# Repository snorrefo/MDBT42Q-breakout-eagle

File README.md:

# MDBT42Q-breakout-eagle
Eagle files for making a breakout board for Raytac's MDBT42Q - nRF52832 based BLE module

Ordered MDBT42Q modules from [Tinysine](https://www.tinyosshop.com/mdbt42-ble-module), due to low shipping to Norway. $7.95 each, plus $4 shipping to Norway. Alternative: [Seed](https://www.seeedstudio.com/MDBT42Q-nRF52832-based-BLE-module-p-2736.html) 

Uploaded MDBT42Q.brd and ordered board from [OSH Park](https://oshpark.com/shared_projects/iggYdmAZ). Link contains shared project, ready for order. $9.80 per batch of three.

Uploaded MDBT42Q.brd and ordered solder stencil and acrylic jig set from [OSH Stencils](https://www.oshstencils.com/) for 10 $ + 5 $ shipping to Norway. Stencil Polyimide Film 3mil (0.003").

Used lead-free solder paste from [SparkFun/Chip Quik](https://www.sparkfun.com/products/12878).

After applying solder paste using the stencil, jig set and solder paste spreader (included in the jig set), the MDBT42Q module was placed gently on top of the solder and board. It doesn't matter much that the solder is smeared a bit, as the reflow will draw the solder to the solder pads. 

The board was placed in an old springform cake tin, and placed on a kitchen stove plate to reflow the solder. Turning the plate on, I used a digital cooking thermometer placed under some tin foil to monitor the cake tin temperature. My thermometer read ca. 223 deg C when the solder paste had reflowed properly. See solder paste data sheet for recommended reflow temperature profile (max 249 deg C). When the solder had reflowed properly, the cake tin was removed from the hot plate to cool. The result:

Using a JTAG programmer, such as the one included on Nordic's [nRF52 Developer Kit](https://www.nordicsemi.com/eng/Products/Bluetooth-low-energy/nRF52-DK), I was able to program the MDBT42Q module. More on that later. See for example 

https://learn.sparkfun.com/tutorials/nrf52832-breakout-board-hookup-guide

https://devzone.nordicsemi.com/f/nordic-q-a/14058/external-programming-using-nrf52-dk

Connecting the nRF52 DK to the MDBT42Q:

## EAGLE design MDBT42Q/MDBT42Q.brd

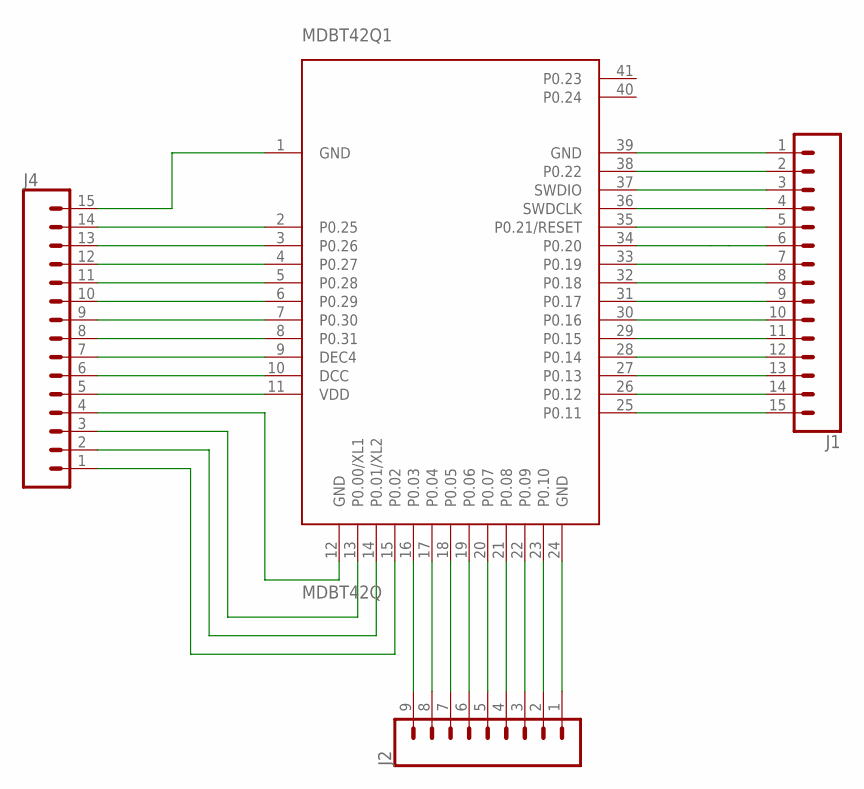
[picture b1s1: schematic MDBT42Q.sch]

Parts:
J1, J4: CONN_15; 1X15
J2: CONN_09; 1X09
MDBT42Q1: MDBT42Q

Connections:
unnamed: J4.15, MDBT42Q1.1 (GND)
unnamed: J4.14, MDBT42Q1.2 (P0.25)
unnamed: J4.13, MDBT42Q1.3 (P0.26)
unnamed: J4.12, MDBT42Q1.4 (P0.27)
unnamed: J4.11, MDBT42Q1.5 (P0.28)
unnamed: J4.10, MDBT42Q1.6 (P0.29)
unnamed: J4.9, MDBT42Q1.7 (P0.30)
unnamed: J4.8, MDBT42Q1.8 (P0.31)
unnamed: J4.7, MDBT42Q1.9 (DEC4)
unnamed: J4.6, MDBT42Q1.10 (DCC)
unnamed: J4.5, MDBT42Q1.11 (VDD)
unnamed: J4.4, MDBT42Q1.12 (GND)
unnamed: J4.3, MDBT42Q1.13 (P0.00/XL1)
unnamed: J4.2, MDBT42Q1.14 (P0.01/XL2)
unnamed: J4.1, MDBT42Q1.15 (P0.02)
unnamed: J2.9, MDBT42Q1.16 (P0.03)
unnamed: J2.8, MDBT42Q1.17 (P0.04)
unnamed: J2.5, MDBT42Q1.20 (P0.07)
unnamed: J2.6, MDBT42Q1.19 (P0.06)
unnamed: J2.7, MDBT42Q1.18 (P0.05)
unnamed: J2.4, MDBT42Q1.21 (P0.08)
unnamed: J2.3, MDBT42Q1.22 (P0.09)
unnamed: J2.2, MDBT42Q1.23 (P0.10)
unnamed: J2.1, MDBT42Q1.24 (GND)
unnamed: J1.15, MDBT42Q1.25 (P0.11)
unnamed: J1.14, MDBT42Q1.26 (P0.12)
unnamed: J1.13, MDBT42Q1.27 (P0.13)
unnamed: J1.12, MDBT42Q1.28 (P0.14)
unnamed: J1.11, MDBT42Q1.29 (P0.15)
unnamed: J1.10, MDBT42Q1.30 (P0.16)
unnamed: J1.9, MDBT42Q1.31 (P0.17)
unnamed: J1.8, MDBT42Q1.32 (P0.18)
unnamed: J1.7, MDBT42Q1.33 (P0.19)
unnamed: J1.6, MDBT42Q1.34 (P0.20)
unnamed: J1.5, MDBT42Q1.35 (P0.21/RESET)
unnamed: J1.4, MDBT42Q1.36 (SWDCLK)
unnamed: J1.3, MDBT42Q1.37 (SWDIO)
unnamed: J1.2, MDBT42Q1.38 (P0.22)
unnamed: J1.1, MDBT42Q1.39 (GND)

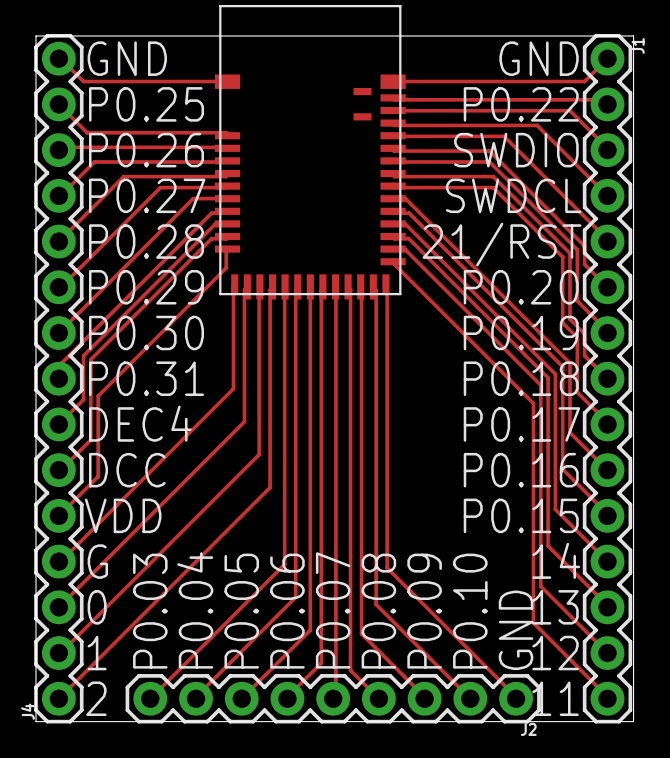
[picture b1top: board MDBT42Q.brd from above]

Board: 2 copper layers, 33.2 x 38.1 mm, 4 parts (0 on the bottom side), 39 nets.

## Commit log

2018-05-01 Eagle files
2018-05-01 Added images
2018-05-01 Renamed file

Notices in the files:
parts and their libraries:
SparkFun-Connectors: Licensing: Creative Commons ShareAlike 4.0 International - https://creativecommons.org/licenses/by-sa/4.0
